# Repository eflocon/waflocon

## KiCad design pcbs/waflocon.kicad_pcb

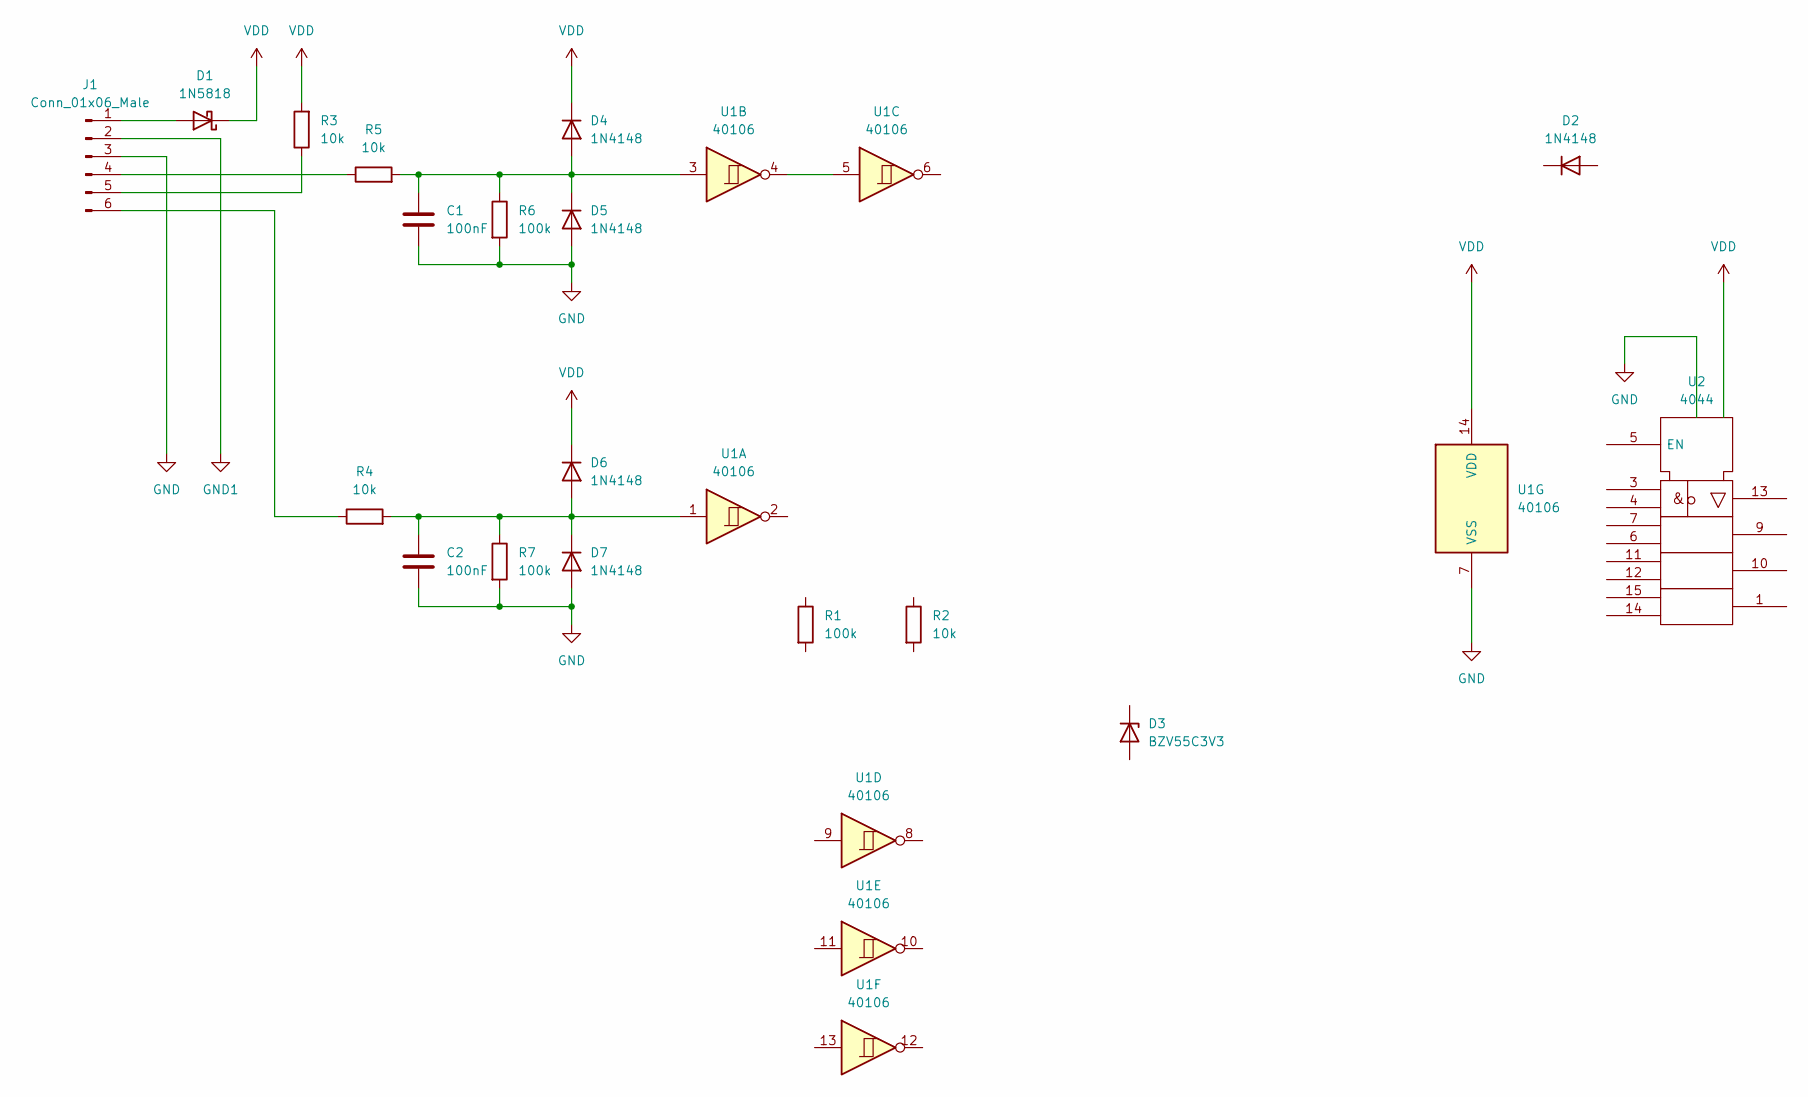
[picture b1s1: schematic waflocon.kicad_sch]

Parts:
C1, C2: 100nF; C_0603_1608Metric
D1: 1N5818; D_DO-41_SOD81_P10.16mm_Horizontal
D2, D4, D5, D6, D7: 1N4148; D_DO-35_SOD27_P7.62mm_Horizontal
D3: BZV55C3V3; D_MiniMELF
J1: Conn_01x06_Male
R1, R6, R7: 100k; R_0603_1608Metric
R2, R3, R4, R5: 10k; R_0603_1608Metric
U1: 40106; DIP-14_W7.62mm_Socket
U2: 4044; DIP-16_W7.62mm_Socket

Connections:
GND: C1.2, C2.2, D5.2 (A), D7.2 (A), J1.3, R6.2, R7.2, U1.7 (VSS), U2.8 (Vss)
unnamed: C1.1, D4.2 (A), D5.1 (K), R5.2, R6.1, U1.3
unnamed: D1.2 (A), J1.1
unnamed: J1.4, R5.1
unnamed: J1.5, R3.1
unnamed: J1.6, R4.1
unnamed: C2.1, D6.2 (A), D7.1 (K), R4.2, R7.1, U1.1
unnamed: U1.4, U1.5
VDD: D1.1 (K), D4.1 (K), D6.1 (K), R3.2, U1.14 (VDD), U2.16 (Vdd)

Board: 2 copper layers, 18 parts (0 on the bottom side), 5 nets, no tracks yet.

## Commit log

2024-02-29 init commit
2024-03-01 DS_Store
2024-03-01 big renaming
2024-03-01 ignore mod
2024-03-01 bugfixing wall dimensions
